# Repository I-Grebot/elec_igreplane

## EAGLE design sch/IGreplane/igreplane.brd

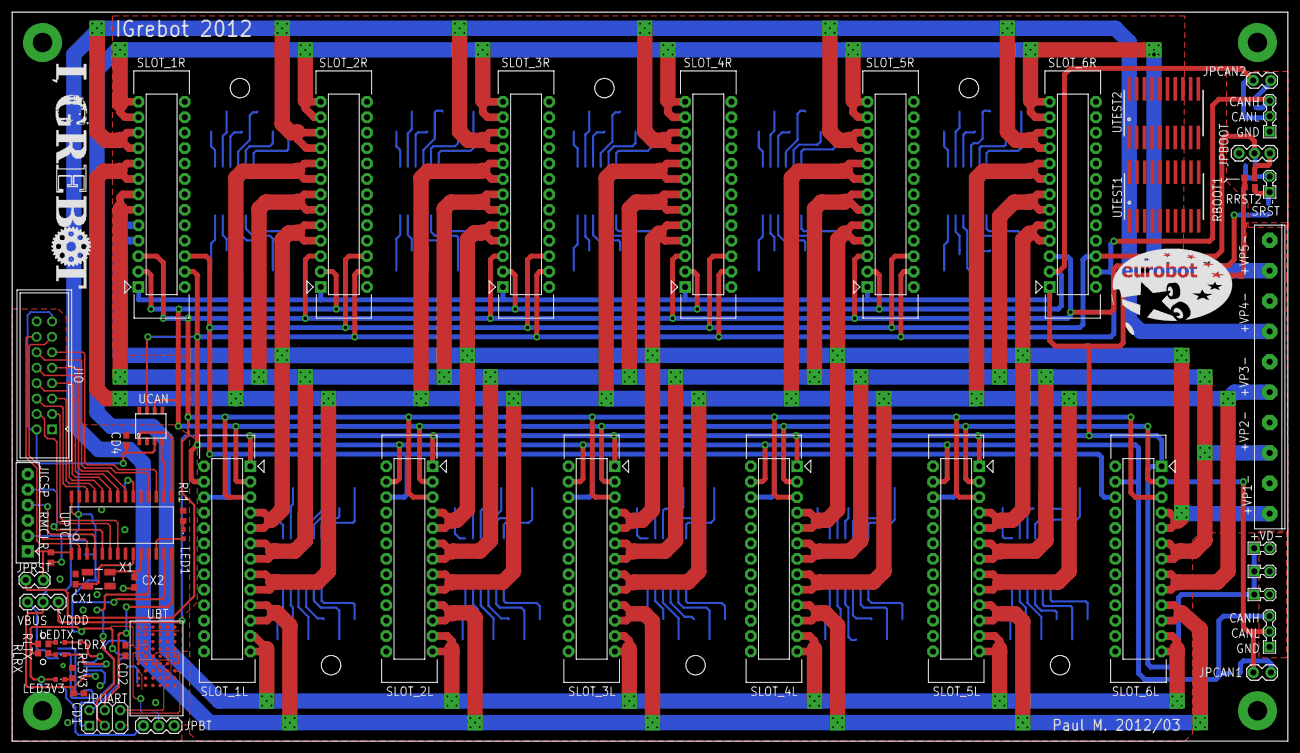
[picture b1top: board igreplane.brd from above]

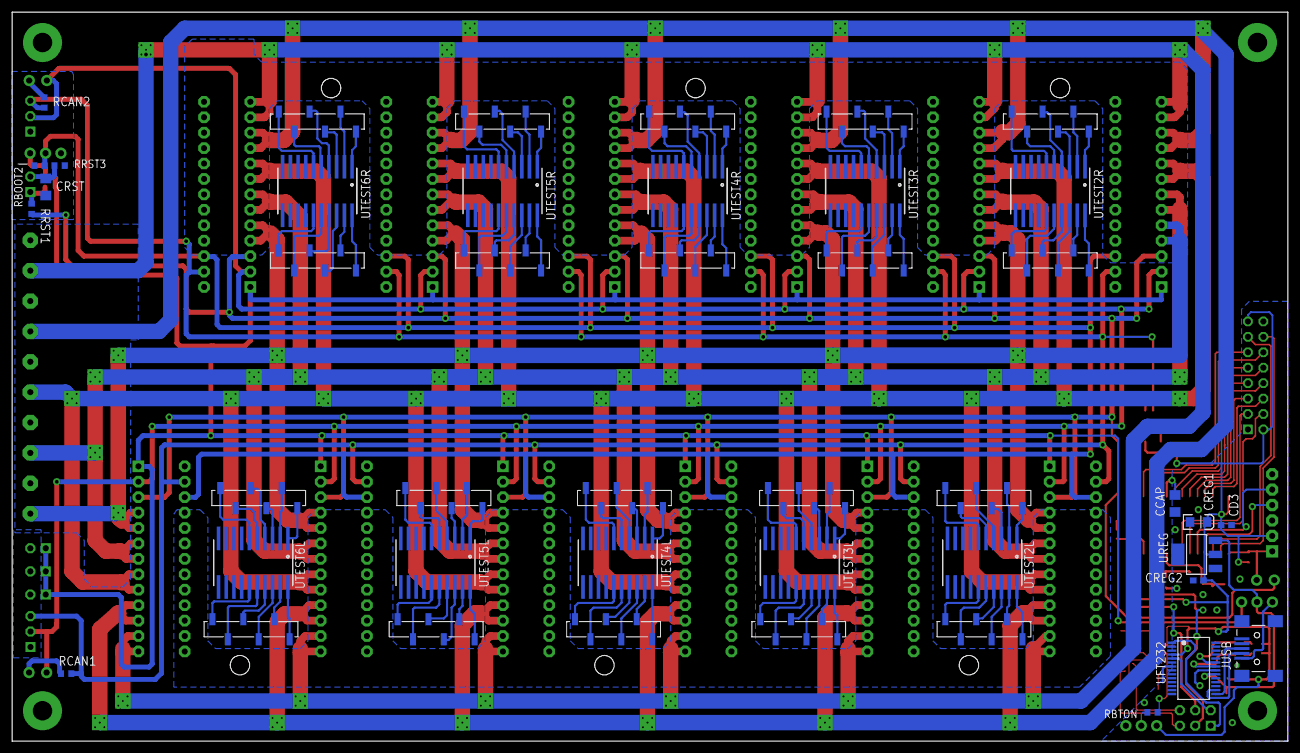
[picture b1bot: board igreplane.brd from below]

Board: 2 copper layers, 210.0 x 120.0 mm, 151 parts (44 on the bottom side), 176 nets.

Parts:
CCAP: 10uF; C1206
CD1, CD2, CD3, CD4: 100nF; C0603
CREG1: 10uF; EIA3216
CREG2: 220nF; C0603
CRST: 100nF; C1206
CX1, CX2: 22pF; C0603
JCAN1, JCAN2: SIL3; CON3-2.54
JICSP: PICKIT_H
JIO: HE10-16; CON-HE10-16-2.54
JPBOOT: JUMPER-3PTH; 1X03
JPBT: JUMPER-3PTH; 1X03
JPCAN1, JPCAN2: 1X02_LOCK
JPRST: 1X02_LOCK
JPUART: SIL2X3; CON2X3-2.54
JPVUSB: JUMPER-3PTH; 1X03
JTEST2L1, JTEST2L2, JTEST2R1, JTEST2R2, JTEST3L1, JTEST3L2, JTEST3R1, JTEST3R2, JTEST4L1, JTEST4L2, JTEST4R1, JTEST4R2, JTEST5L1, JTEST5R1, JTEST5R2, JTEST6L1, JTEST6R1, JTEST6R2, JTEST25L2, JTEST26L2: 1X06_SMD_STRAIGHT_ALT
JUSB: USBSMD; USB-MINIB
JVDDD1, JVDDD2, JVDDD3: SIL2; CON2-2.54
JVDDP: MULTICOMP_PA001-10; CON10-5.00
LED1, LED3V3: CHIPLED_0603
LEDRX: CHIPLED_0603
LEDTX: CHIPLED_0603
RBOOT1: 2k7; R0603
RBOOT2: 4k7; R0603
RBTON: 3.3k; R0603
RCAN1, RCAN2: 120; R0603
RL1, RL3V3: 270; R0603
RLRX: 270; R0603
RLTX: 270; R0603
RMCLR: 4.7k; R0603
RRST1: 100; R0603
RRST2: 2k7; R0603
RRST3: 4.7k; R0603
SLOT_1L, SLOT_1R, SLOT_2L, SLOT_2R, SLOT_3L, SLOT_3R, SLOT_4L, SLOT_4R, SLOT_5L, SLOT_5R, SLOT_6L, SLOT_6R: CON_IGREPLANE_SOCKET; CON_WURTH_6130_26_216921
SRST: SIL2; CON2-2.54
U$1, U$2, U$3, U$4, U$5, U$6, U$7, U$8, U$9, U$10, U$11, U$12, U$13, U$14, U$15, U$16, U$17, U$18, U$19, U$20, U$21, U$22, U$23, U$24, U$25, U$26, U$27, U$28, U$29, U$30, U$31, U$32, U$33, U$34, U$35, U$37, U$38, U$39, U$40, U$41, U$42, U$43, U$44, U$45, U$46, U$47, U$48, U$49, U$50, U$51, U$52, U$53, U$54, U$55, U$56, U$57, U$58: VIA-5_0.3
UBT: PANASONIC_PAN1321-SPP; BGA53_PAN1321-SSP
UCAN: SN65HVD231Q; SOIC8
UFT232: FT232RL; SSOP28
UPIC: DSPIC33FJ128MC802-SO; SOIC28
UREG: V_REG_317SMD; SOT223
UTEST1, UTEST2, UTEST2L, UTEST2R, UTEST3L, UTEST3R, UTEST4L, UTEST4R, UTEST5L, UTEST5R, UTEST6L, UTEST6R: SOIC_20; SO20W
X1: CRYSTAL-SMD-5X3

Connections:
!MCLR: JICSP.1, JPRST.2, RMCLR.1, UPIC.1
!RESET!: JPRST.1, RRST1.2, SLOT_1L.5, SLOT_1R.5, SLOT_2L.5, SLOT_2R.5, SLOT_3L.5, SLOT_3R.5, SLOT_4L.5, SLOT_4R.5, SLOT_5L.5, SLOT_5R.5, SLOT_6L.5, SLOT_6R.5
+3V3: CD2.1, CD3.1, CD4.1, CREG1.A, CREG2.1, JICSP.2, JIO.2, JIO.15, JPBT.1, LED3V3.A, RLRX.2, RLTX.2, RMCLR.2, UBT.A3, UBT.A4, UBT.A5, UBT.A6, UBT.C5, UBT.F6, UCAN.3, UFT232.4, UPIC.13, UPIC.28, UREG.2
BOOTSTRAP: JPBOOT.2, RBOOT2.2, SLOT_1L.6, SLOT_1R.6, SLOT_2L.6, SLOT_2R.6, SLOT_3L.6, SLOT_3R.6, SLOT_4L.6, SLOT_4R.6, SLOT_5L.6, SLOT_5R.6, SLOT_6L.6, SLOT_6R.6
BT_ON: RBTON.1, UBT.B5
BT_RXD: JPUART.6, UBT.E6
BT_TXD: JPUART.5, UBT.F7
CANH: JCAN1.3, JCAN2.3, RCAN1.1, RCAN2.1, SLOT_1L.4, SLOT_1R.4, SLOT_2L.4, SLOT_2R.4, SLOT_3L.4, SLOT_3R.4, SLOT_4L.4, SLOT_4R.4, SLOT_5L.4, SLOT_5R.4, SLOT_6L.4, SLOT_6R.4, UCAN.7
CANL: JCAN1.2, JCAN2.2, JPCAN1.2, JPCAN2.2, SLOT_1L.3, SLOT_1R.3, SLOT_2L.3, SLOT_2R.3, SLOT_3L.3, SLOT_3R.3, SLOT_4L.3, SLOT_4R.3, SLOT_5L.3, SLOT_5R.3, SLOT_6L.3, SLOT_6R.3, UCAN.6
CAN_RXD: UCAN.4, UPIC.16
CAN_TXD: UCAN.1, UPIC.15
FTDI_RXD: JPUART.2, UFT232.5
FTDI_TXD: JPUART.1, UFT232.1
GND: CCAP.2, CD1.2, CD2.2, CD3.2, CD4.2, CREG1.C, CREG2.2, CRST.2, CX1.2, CX2.2, JCAN1.1, JCAN2.1, JICSP.3, JIO.1, JIO.16, JPBOOT.3, JPBT.3, JUSB.GND, JVDDD1.2, JVDDD2.2, JVDDD3.2, JVDDP.2, JVDDP.4, JVDDP.6, JVDDP.8, JVDDP.10, RBOOT2.1, RL1.1, RL3V3.1, RRST3.1, SLOT_1L.2, SLOT_1L.8, SLOT_1L.10, SLOT_1L.12, SLOT_1L.14, SLOT_1L.16, SLOT_1L.18, SLOT_1L.20, SLOT_1L.22, SLOT_1L.24, SLOT_1L.26, SLOT_1R.2, SLOT_1R.8, SLOT_1R.10, SLOT_1R.12, SLOT_1R.14, SLOT_1R.16, SLOT_1R.18, SLOT_1R.20, SLOT_1R.22, SLOT_1R.24, SLOT_1R.26, SLOT_2L.2, SLOT_2L.8, SLOT_2L.10, SLOT_2L.12, SLOT_2L.14, SLOT_2L.16, SLOT_2L.18, SLOT_2L.20, SLOT_2L.22, SLOT_2L.24, SLOT_2L.26, SLOT_2R.2, SLOT_2R.8, SLOT_2R.10, SLOT_2R.12, SLOT_2R.14, SLOT_2R.16, SLOT_2R.18, SLOT_2R.20, SLOT_2R.22, SLOT_2R.24, SLOT_2R.26, SLOT_3L.2, SLOT_3L.8, SLOT_3L.10, SLOT_3L.12, SLOT_3L.14, SLOT_3L.16, SLOT_3L.18, SLOT_3L.20, SLOT_3L.22, SLOT_3L.24, SLOT_3L.26, SLOT_3R.2, SLOT_3R.8, SLOT_3R.10, SLOT_3R.12, SLOT_3R.14, SLOT_3R.16, SLOT_3R.18, SLOT_3R.20, SLOT_3R.22, SLOT_3R.24, SLOT_3R.26, SLOT_4L.2, SLOT_4L.8, SLOT_4L.10, SLOT_4L.12, SLOT_4L.14, SLOT_4L.16, SLOT_4L.18, SLOT_4L.20, SLOT_4L.22, SLOT_4L.24, SLOT_4L.26, SLOT_4R.2, SLOT_4R.8, SLOT_4R.10, SLOT_4R.12, SLOT_4R.14, SLOT_4R.16, SLOT_4R.18, SLOT_4R.20, SLOT_4R.22, SLOT_4R.24, SLOT_4R.26, SLOT_5L.2, SLOT_5L.8, SLOT_5L.10, SLOT_5L.12, SLOT_5L.14, SLOT_5L.16, SLOT_5L.18, SLOT_5L.20, SLOT_5L.22, SLOT_5L.24, SLOT_5L.26, SLOT_5R.2, SLOT_5R.8, SLOT_5R.10, SLOT_5R.12, SLOT_5R.14, SLOT_5R.16, SLOT_5R.18, SLOT_5R.20, SLOT_5R.22, SLOT_5R.24, SLOT_5R.26, SLOT_6L.2, SLOT_6L.8, SLOT_6L.10, SLOT_6L.12, SLOT_6L.14, SLOT_6L.16, SLOT_6L.18, SLOT_6L.20, SLOT_6L.22, SLOT_6L.24, SLOT_6L.26, SLOT_6R.2, SLOT_6R.8, SLOT_6R.10, SLOT_6R.12, SLOT_6R.14, SLOT_6R.16, SLOT_6R.18, SLOT_6R.20, SLOT_6R.22, SLOT_6R.24, SLOT_6R.26, UBT.A1, UBT.A7, UBT.A9, UBT.C8, UBT.C9, UBT.D7, UBT.D8, UBT.E8, UBT.E9, UBT.F1, UBT.F9, UCAN.2, UFT232.7, UFT232.18, UFT232.21, UFT232.25, UFT232.26, UPIC.8, UPIC.19, UPIC.27, UREG.1
IO1: JIO.3, UPIC.7
IO2: JIO.4, UPIC.6
IO3: JIO.5, UPIC.25
IO4: JIO.6, UPIC.26
IO5: JIO.7, UPIC.23
IO6: JIO.8, UPIC.24
IO7: JIO.9, UPIC.21
IO8: JIO.10, UPIC.22
IO9: JIO.11, UPIC.17
IO10: JIO.12, UPIC.18
IO11: JIO.13, UPIC.3
IO12: JIO.14, UPIC.2
LED1: LED1.A, UPIC.12
unnamed: JPCAN1.1, RCAN1.2
unnamed: CRST.1, RRST3.2, SRST.2
unnamed: RRST1.1, RRST2.1, SRST.1
unnamed: JPCAN2.1, RCAN2.2
unnamed: LEDTX.C, UFT232.23
unnamed: JPBOOT.1, RBOOT1.1
unnamed: LEDRX.C, UFT232.22
unnamed: LEDTX.A, RLTX.1
unnamed: LEDRX.A, RLRX.1
unnamed: LED1.C, RL1.2
unnamed: LED3V3.C, RL3V3.2
unnamed: JPBT.2, RBTON.2
unnamed: JTEST6R2.1, UTEST6R.P$20
unnamed: JTEST6R2.2, UTEST6R.P$19
unnamed: JTEST6R2.3, UTEST6R.P$18
unnamed: JTEST6R2.4, UTEST6R.P$17
unnamed: JTEST6R2.5, UTEST6R.P$16
unnamed: JTEST6R2.6, UTEST6R.P$15
unnamed: JTEST6R1.1, UTEST6R.P$6
unnamed: JTEST6R1.2, UTEST6R.P$5
unnamed: JTEST6R1.3, UTEST6R.P$4
unnamed: JTEST6R1.4, UTEST6R.P$3
unnamed: JTEST6R1.5, UTEST6R.P$2
unnamed: JTEST6R1.6, UTEST6R.P$1
unnamed: JTEST5R2.1, UTEST5R.P$20
unnamed: JTEST5R2.2, UTEST5R.P$19
unnamed: JTEST5R2.3, UTEST5R.P$18
unnamed: JTEST5R2.4, UTEST5R.P$17
unnamed: JTEST5R2.5, UTEST5R.P$16
unnamed: JTEST5R2.6, UTEST5R.P$15
unnamed: JTEST5R1.1, UTEST5R.P$6
unnamed: JTEST5R1.2, UTEST5R.P$5
unnamed: JTEST5R1.3, UTEST5R.P$4
unnamed: JTEST5R1.4, UTEST5R.P$3
unnamed: JTEST5R1.5, UTEST5R.P$2
unnamed: JTEST5R1.6, UTEST5R.P$1
unnamed: JTEST4R2.1, UTEST4R.P$20
unnamed: JTEST4R2.2, UTEST4R.P$19
unnamed: JTEST4R2.3, UTEST4R.P$18
unnamed: JTEST4R2.4, UTEST4R.P$17
unnamed: JTEST4R2.5, UTEST4R.P$16
unnamed: JTEST4R2.6, UTEST4R.P$15
unnamed: JTEST4R1.1, UTEST4R.P$6
unnamed: JTEST4R1.2, UTEST4R.P$5
unnamed: JTEST4R1.3, UTEST4R.P$4
unnamed: JTEST4R1.4, UTEST4R.P$3
unnamed: JTEST4R1.5, UTEST4R.P$2
unnamed: JTEST4R1.6, UTEST4R.P$1
unnamed: JTEST3R2.1, UTEST3R.P$20
unnamed: JTEST3R2.2, UTEST3R.P$19
unnamed: JTEST3R2.3, UTEST3R.P$18
unnamed: JTEST3R2.4, UTEST3R.P$17
unnamed: JTEST3R2.5, UTEST3R.P$16
unnamed: JTEST3R2.6, UTEST3R.P$15
unnamed: JTEST3R1.1, UTEST3R.P$6
unnamed: JTEST3R1.2, UTEST3R.P$5
unnamed: JTEST3R1.3, UTEST3R.P$4
unnamed: JTEST3R1.4, UTEST3R.P$3
unnamed: JTEST3R1.5, UTEST3R.P$2
unnamed: JTEST3R1.6, UTEST3R.P$1
unnamed: JTEST2R2.1, UTEST2R.P$20
unnamed: JTEST2R2.2, UTEST2R.P$19
unnamed: JTEST2R2.3, UTEST2R.P$18
unnamed: JTEST2R2.4, UTEST2R.P$17
unnamed: JTEST2R2.5, UTEST2R.P$16
unnamed: JTEST2R2.6, UTEST2R.P$15
unnamed: JTEST2R1.1, UTEST2R.P$6
unnamed: JTEST2R1.2, UTEST2R.P$5
unnamed: JTEST2R1.3, UTEST2R.P$4
unnamed: JTEST2R1.4, UTEST2R.P$3
unnamed: JTEST2R1.5, UTEST2R.P$2
unnamed: JTEST2R1.6, UTEST2R.P$1
unnamed: JTEST2L1.1, UTEST2L.P$6
unnamed: JTEST2L1.2, UTEST2L.P$5
unnamed: JTEST2L1.3, UTEST2L.P$4
unnamed: JTEST2L1.4, UTEST2L.P$3
unnamed: JTEST2L1.5, UTEST2L.P$2
unnamed: JTEST2L1.6, UTEST2L.P$1
unnamed: JTEST3L1.1, UTEST3L.P$6
unnamed: JTEST3L1.2, UTEST3L.P$5
unnamed: JTEST3L1.3, UTEST3L.P$4
unnamed: JTEST3L1.4, UTEST3L.P$3
unnamed: JTEST3L1.5, UTEST3L.P$2
unnamed: JTEST3L1.6, UTEST3L.P$1
unnamed: JTEST4L1.1, UTEST4L.P$6
unnamed: JTEST4L1.2, UTEST4L.P$5
unnamed: JTEST4L1.3, UTEST4L.P$4
unnamed: JTEST4L1.4, UTEST4L.P$3
unnamed: JTEST4L1.5, UTEST4L.P$2
unnamed: JTEST4L1.6, UTEST4L.P$1
unnamed: JTEST5L1.1, UTEST5L.P$6
unnamed: JTEST5L1.2, UTEST5L.P$5
unnamed: JTEST5L1.3, UTEST5L.P$4
unnamed: JTEST5L1.4, UTEST5L.P$3
unnamed: JTEST5L1.5, UTEST5L.P$2
unnamed: JTEST5L1.6, UTEST5L.P$1
unnamed: JTEST6L1.1, UTEST6L.P$6
unnamed: JTEST6L1.2, UTEST6L.P$5
unnamed: JTEST6L1.3, UTEST6L.P$4
unnamed: JTEST6L1.4, UTEST6L.P$3
unnamed: JTEST6L1.5, UTEST6L.P$2
unnamed: JTEST6L1.6, UTEST6L.P$1
unnamed: JTEST2L2.1, UTEST2L.P$20
unnamed: JTEST2L2.2, UTEST2L.P$19
unnamed: JTEST2L2.3, UTEST2L.P$18
unnamed: JTEST2L2.4, UTEST2L.P$17
unnamed: JTEST2L2.5, UTEST2L.P$16
unnamed: JTEST2L2.6, UTEST2L.P$15
unnamed: JTEST3L2.1, UTEST3L.P$20
unnamed: JTEST3L2.2, UTEST3L.P$19
unnamed: JTEST3L2.3, UTEST3L.P$18
unnamed: JTEST3L2.4, UTEST3L.P$17
unnamed: JTEST3L2.5, UTEST3L.P$16
unnamed: JTEST3L2.6, UTEST3L.P$15
unnamed: JTEST4L2.1, UTEST4L.P$20
unnamed: JTEST4L2.2, UTEST4L.P$19
unnamed: JTEST4L2.3, UTEST4L.P$18
unnamed: JTEST4L2.4, UTEST4L.P$17
unnamed: JTEST4L2.5, UTEST4L.P$16
unnamed: JTEST4L2.6, UTEST4L.P$15
unnamed: JTEST25L2.1, UTEST5L.P$20
unnamed: JTEST25L2.2, UTEST5L.P$19
unnamed: JTEST25L2.3, UTEST5L.P$18
unnamed: JTEST25L2.4, UTEST5L.P$17
unnamed: JTEST25L2.5, UTEST5L.P$16
unnamed: JTEST25L2.6, UTEST5L.P$15
unnamed: JTEST26L2.1, UTEST6L.P$20
unnamed: JTEST26L2.2, UTEST6L.P$19
unnamed: JTEST26L2.3, UTEST6L.P$18
unnamed: JTEST26L2.4, UTEST6L.P$17
unnamed: JTEST26L2.5, UTEST6L.P$16
unnamed: JTEST26L2.6, UTEST6L.P$15
OSC1: CX1.1, UPIC.9, X1.1
OSC2: CX2.1, UPIC.10, X1.3
PGC: JICSP.5, UPIC.5
PGD: JICSP.4, UPIC.4
UART_RXD: JPUART.4, UPIC.14
UART_TXD: JPUART.3, UPIC.11
USBDM: JUSB.D-, UFT232.16
USBDP: JUSB.D+, UFT232.15
VBUS: JPVUSB.1, JUSB.VBUS
VCAP: CCAP.1, UPIC.20
VDDD: JPVUSB.3, JVDDD1.1, JVDDD2.1, JVDDD3.1, RBOOT1.2, RRST2.2, SLOT_1L.1, SLOT_1R.1, SLOT_2L.1, SLOT_2R.1, SLOT_3L.1, SLOT_3R.1, SLOT_4L.1, SLOT_4R.1, SLOT_5L.1, SLOT_5R.1, SLOT_6L.1, SLOT_6R.1
VDDP1: JVDDP.1, SLOT_1L.7, SLOT_1L.9, SLOT_1R.7, SLOT_1R.9, SLOT_2L.7, SLOT_2L.9, SLOT_2R.7, SLOT_2R.9, SLOT_3L.7, SLOT_3L.9, SLOT_3R.7, SLOT_3R.9, SLOT_4L.7, SLOT_4L.9, SLOT_4R.7, SLOT_4R.9, SLOT_5L.7, SLOT_5L.9, SLOT_5R.7, SLOT_5R.9, SLOT_6L.7, SLOT_6L.9, SLOT_6R.7, SLOT_6R.9, U$25.VIA, U$26.VIA, U$27.VIA, U$28.VIA, U$29.VIA, U$30.VIA, U$57.VIA
VDDP2: JVDDP.3, SLOT_1L.11, SLOT_1L.13, SLOT_1R.11, SLOT_1R.13, SLOT_2L.11, SLOT_2L.13, SLOT_2R.11, SLOT_2R.13, SLOT_3L.11, SLOT_3L.13, SLOT_3R.11, SLOT_3R.13, SLOT_4L.11, SLOT_4L.13, SLOT_4R.11, SLOT_4R.13, SLOT_5L.11, SLOT_5L.13, SLOT_5R.11, SLOT_5R.13, SLOT_6L.11, SLOT_6L.13, SLOT_6R.11, SLOT_6R.13, U$31.VIA, U$32.VIA, U$33.VIA, U$34.VIA, U$35.VIA, U$37.VIA, U$38.VIA, U$39.VIA, U$40.VIA, U$41.VIA, U$42.VIA, U$43.VIA, U$56.VIA
VDDP3: JVDDP.5, SLOT_1L.15, SLOT_1L.17, SLOT_1R.15, SLOT_1R.17, SLOT_2L.15, SLOT_2L.17, SLOT_2R.15, SLOT_2R.17, SLOT_3L.15, SLOT_3L.17, SLOT_3R.15, SLOT_3R.17, SLOT_4L.15, SLOT_4L.17, SLOT_4R.15, SLOT_4R.17, SLOT_5L.15, SLOT_5L.17, SLOT_5R.15, SLOT_5R.17, SLOT_6L.15, SLOT_6L.17, SLOT_6R.15, SLOT_6R.17, U$44.VIA, U$45.VIA, U$46.VIA, U$47.VIA, U$48.VIA, U$49.VIA, U$50.VIA, U$51.VIA, U$52.VIA, U$53.VIA, U$54.VIA, U$55.VIA
VDDP4: JVDDP.7, SLOT_1L.19, SLOT_1L.21, SLOT_1R.19, SLOT_1R.21, SLOT_2L.19, SLOT_2L.21, SLOT_2R.19, SLOT_2R.21, SLOT_3L.19, SLOT_3L.21, SLOT_3R.19, SLOT_3R.21, SLOT_4L.19, SLOT_4L.21, SLOT_4R.19, SLOT_4R.21, SLOT_5L.19, SLOT_5L.21, SLOT_5R.19, SLOT_5R.21, SLOT_6L.19, SLOT_6L.21, SLOT_6R.19, SLOT_6R.21, U$1.VIA, U$2.VIA, U$3.VIA, U$4.VIA, U$5.VIA, U$6.VIA, U$7.VIA, U$8.VIA, U$9.VIA, U$10.VIA, U$11.VIA, U$12.VIA
VDDP5: JVDDP.9, SLOT_1L.23, SLOT_1L.25, SLOT_1R.23, SLOT_1R.25, SLOT_2L.23, SLOT_2L.25, SLOT_2R.23, SLOT_2R.25, SLOT_3L.23, SLOT_3L.25, SLOT_3R.23, SLOT_3R.25, SLOT_4L.23, SLOT_4L.25, SLOT_4R.23, SLOT_4R.25, SLOT_5L.23, SLOT_5L.25, SLOT_5R.23, SLOT_5R.25, SLOT_6L.23, SLOT_6L.25, SLOT_6R.23, SLOT_6R.25, U$13.VIA, U$14.VIA, U$15.VIA, U$16.VIA, U$17.VIA, U$18.VIA, U$19.VIA, U$20.VIA, U$21.VIA, U$22.VIA, U$23.VIA, U$24.VIA, U$58.VIA
VUSB: CD1.1, JPVUSB.2, UFT232.20, UREG.3
